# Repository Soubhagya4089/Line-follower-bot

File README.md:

# Line-follower-bot
A line follower robot is a type of autonomous robot designed to follow a path or track a line
 on the ground. These robots are equipped with IR sensors, which can detect the contrast
 between the white and black surfaces. The primary objective of a line follower robot is to
 navigate and move along the path by adjusting its movements based on the feedback
 received from the sensors.

 The working principle of a line follower robot involves using the sensor data to make
 decisions about the robot's movement. When the sensors detect the line, the robot adjusts
 its direction to stay on course. If the sensors detect a deviation from the line, the robot
 responds by making corrections to realign itself with the path

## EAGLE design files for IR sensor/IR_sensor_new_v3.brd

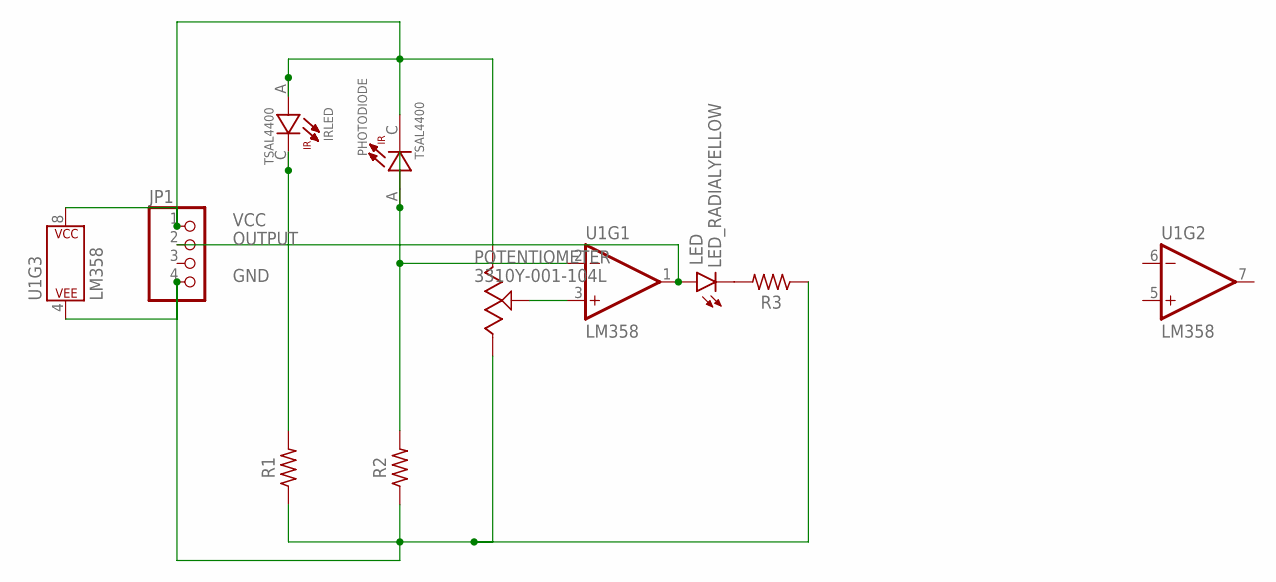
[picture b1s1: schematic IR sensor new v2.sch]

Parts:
IRLED: TSAL4400; LEDRD254W45D335H610
JP1: PINHD-1X4/90; 1X04/90
LED: LED_RADIALYELLOW; LEDRD254W60D565H860B_Y
PHOTODIODE: TSAL4400; LEDRD254W45D335H610
POTENTIOMETER: 3310Y-001-104L; 3310Y-001-104L-ND
R1, R2, R3: R-US_AXIAL-7.2MM-PITCH; RESAD724W46L381D178B
U1: LM358; DIP08-KIT

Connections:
GND: JP1.4, POTENTIOMETER.3, R1.1, R2.1, R3.1, U1.4 (P$V-)
unnamed: IRLED.C, R1.2
unnamed: PHOTODIODE.A, R2.2, U1.2 (-IN)
unnamed: LED.C, R3.2
unnamed: POTENTIOMETER.2, U1.3 (+IN)
OUTPUT: JP1.2, LED.A, U1.1 (OUT)
VCC: IRLED.A, JP1.1, PHOTODIODE.C, POTENTIOMETER.1, U1.8 (P$V+)

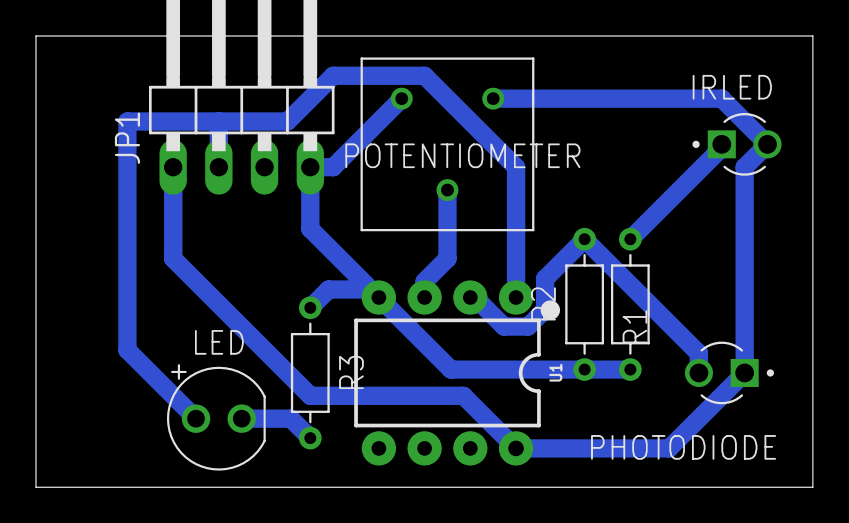
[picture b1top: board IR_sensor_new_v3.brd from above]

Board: 2 copper layers, 43.2 x 25.1 mm, 9 parts (0 on the bottom side), 7 nets.

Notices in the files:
parts and their libraries:
SparkFun-IC-Amplifiers: Licensing: Creative Commons ShareAlike 4.0 International - https://creativecommons.org/licenses/by-sa/4.0
